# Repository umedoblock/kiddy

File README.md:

# kiddy
some simple device projects designed with KiCad.

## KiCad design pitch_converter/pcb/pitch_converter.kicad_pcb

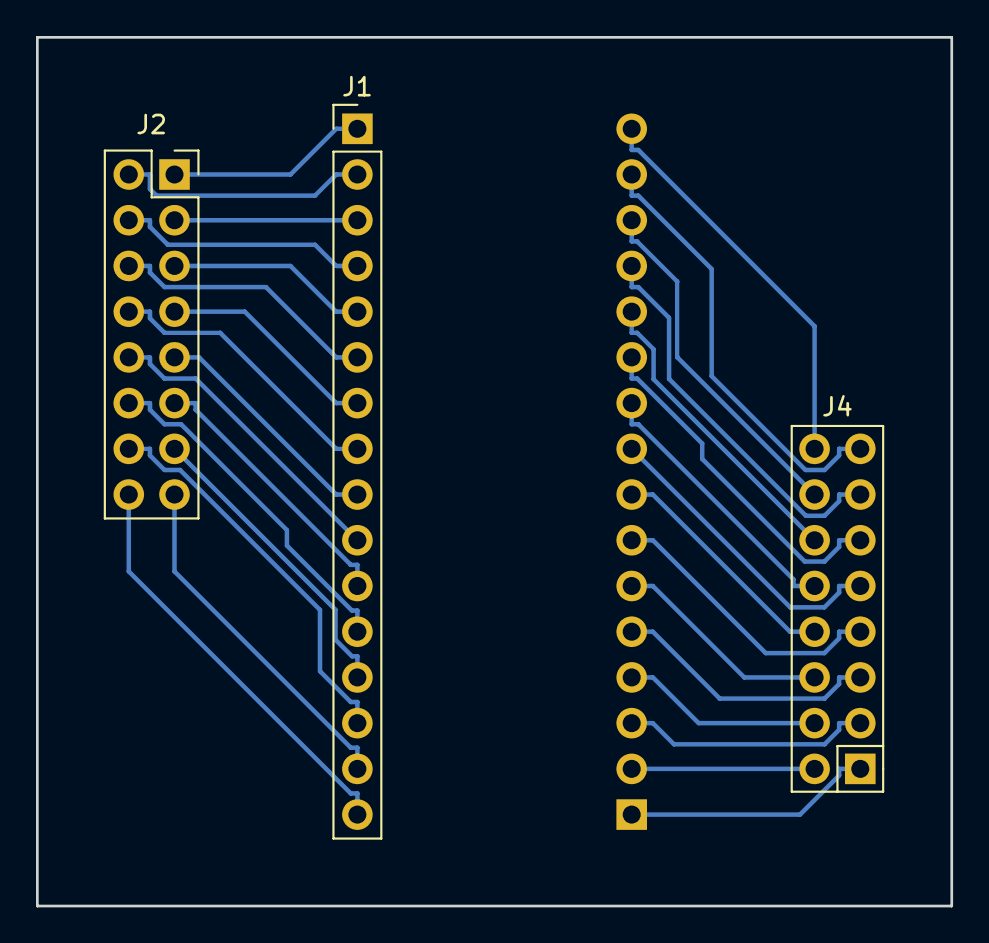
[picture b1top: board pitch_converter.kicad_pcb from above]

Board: 2 copper layers, 50.8 x 48.3 mm, 4 parts (1 on the bottom side), 32 nets.

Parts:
J1, J3: CONN_01X16; PinHeader_1x16_P2.54mm_Vertical
J2: CONN_02X08; PinSocket_2x08_P2.54mm_Vertical
J4: CONN_02X08; PinSocket_2x08_P2.54mm_Vertical_R

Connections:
/C0_1: J1.1, J2.1
/C0_2: J1.2, J2.2
/C0_3: J1.3, J2.3
/C0_4: J1.4, J2.4
/C0_5: J1.5, J2.5
/C0_6: J1.6, J2.6
/C0_7: J1.7, J2.7
/C0_8: J1.8, J2.8
/C0_9: J1.9, J2.9
/C0_10: J1.10, J2.10
/C0_11: J1.11, J2.11
/C0_12: J1.12, J2.12
/C0_13: J1.13, J2.13
/C0_14: J1.14, J2.14
/C0_15: J1.15, J2.15
/C0_16: J1.16, J2.16
/C1_1: J3.1, J4.1
/C1_2: J3.2, J4.2
/C1_3: J3.3, J4.3
/C1_4: J3.4, J4.4
/C1_5: J3.5, J4.5
/C1_6: J3.6, J4.6
/C1_7: J3.7, J4.7
/C1_8: J3.8, J4.8
/C1_9: J3.9, J4.9
/C1_10: J3.10, J4.10
/C1_11: J3.11, J4.11
/C1_12: J3.12, J4.12
/C1_13: J3.13, J4.13
/C1_14: J3.14, J4.14
/C1_15: J3.15, J4.15
/C1_16: J3.16, J4.16

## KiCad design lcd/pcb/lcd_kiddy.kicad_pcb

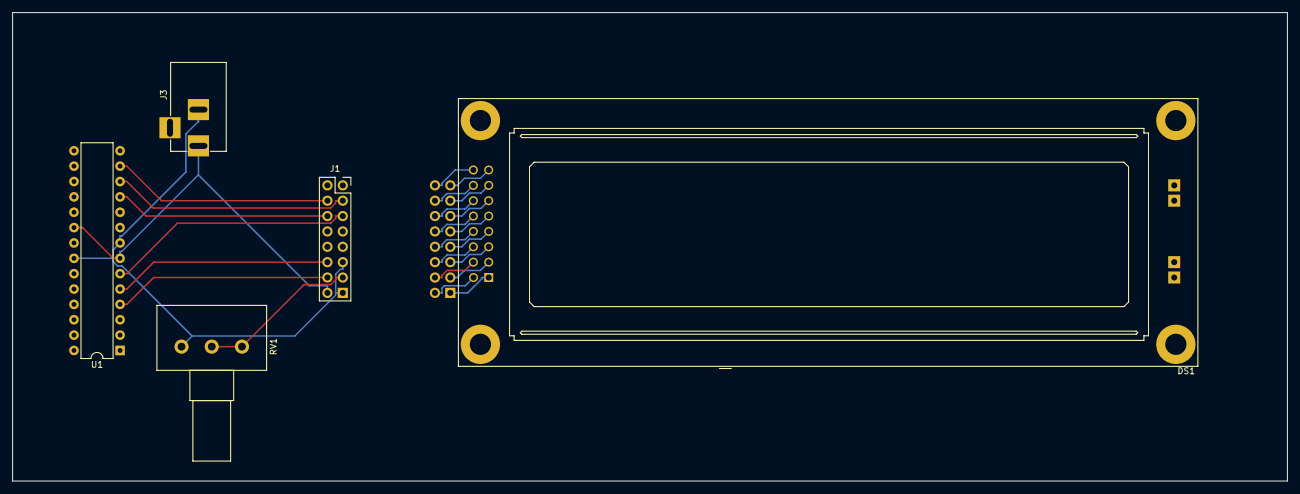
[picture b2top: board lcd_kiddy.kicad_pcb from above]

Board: 2 copper layers, 210.8 x 77.5 mm, 6 parts (1 on the bottom side), 25 nets.

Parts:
DS1: LCD8X2; LCD-2x8-AK
J1: CONN_02X08; PinSocket_2x08_P2.54mm_Vertical_R
J2: CONN_02X08; PinHeader_2x08_P2.54mm_Vertical_R
J3: BARREL_JACK
RV1: 5k; Potentiometer_Alps_RK163_Single_Horizontal
U1: ATMEGA328-PU; DIP-28_W7.62mm

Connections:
+5V: J1.2, J3.1, U1.7, U1.20
/D0: DS1.7, J2.7
/D1: DS1.8, J2.8
/D2: DS1.9, J2.9
/D3: DS1.10, J2.10
/D4: DS1.11, J2.11
/D5: DS1.12, J2.12
/D6: DS1.13, J2.13
/D7: DS1.14, J2.14
/E: DS1.6, J2.6
/LED+: DS1.15, J2.15
/LED-: DS1.16, J2.16
/PD2: J1.4, U1.4
/PD3: J1.6, U1.5
/PD4: J1.11, U1.6
/PD5: J1.12, U1.11
/PD6: J1.13, U1.12
/PD7: J1.14, U1.13
/R/W: DS1.5, J2.5
/RS: DS1.4, J2.4
/VDD: DS1.2, J2.2
/VEE: DS1.3, J2.3
/VSS: DS1.1, J2.1
GND: J1.1, J1.5, J3.2, RV1.1, U1.8, U1.22
unnamed: J1.3, RV1.2, RV1.3

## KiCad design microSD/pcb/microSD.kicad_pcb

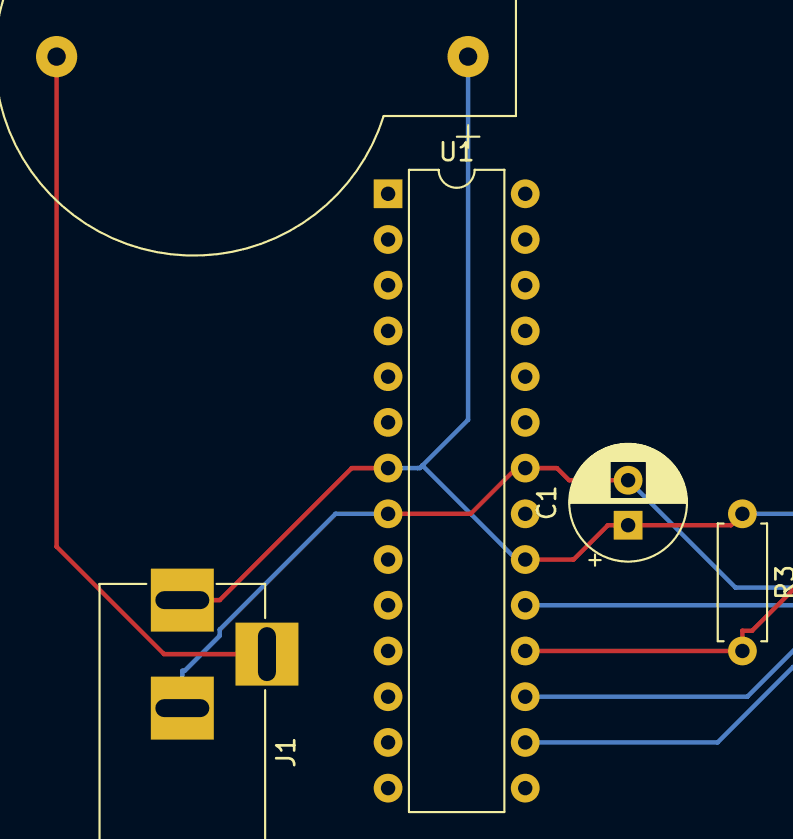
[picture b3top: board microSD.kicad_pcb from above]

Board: 2 copper layers, 6 parts (1 on the bottom side), 7 nets.

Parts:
BT1: Battery_Cell; BatteryHolder_CR2032H
C1: 1u; CP_Radial_D6.3mm_P2.50mm
J1: BARREL_JACK
J4: Micro_SD_Card_Det_SPI; microSD_HC_Hirose_DM3AT-SF-PEJM5
R3: 10k; R_Axial_DIN0207_L6.3mm_D2.5mm_P7.62mm_Horizontal
U1: ATMEGA328P-PU; DIP-28_W7.62mm

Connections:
+3V3: BT1.1, C1.1, J1.1, J4.4, R3.1, U1.7, U1.20
/MISO: J4.7, R3.2, U1.18
/MOSI: J4.3, U1.17
/SCLK: J4.5, U1.19
/_SS: J4.2, U1.16
GND: C1.2, J1.2, J4.6, U1.8, U1.22
unnamed: BT1.2, J1.3

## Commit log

2018-01-03 add tiny comment.
2018-01-03 set ignore files about KiCad.
2018-01-03 pcb files to make a board. eeschema is completed.
2018-01-07 chaN library.
2018-01-18 20x02 のLCDに対応。
2018-01-18 bus 幅を4に設定。
2018-01-18 一旦，LCDの制御boardは完成とする。
2018-01-18 引っ越し。
2018-01-18 basic lcd kiddy files.
2018-01-19 change one tab to four spaces.
2018-01-19 現状，上段の全ての桁に黒四角が表示される。書き込み成功版。
2018-01-19 unsigned char の上位4bitを逆順にする。下位4bitは0で埋める。
    出力は以下の通り。
    d[ 0]=0b00000000, r[ 0]=0b00000000
    d[ 1]=0b00010000, r[ 1]=0b10000000
    d[ 2]=0b00100000, r[ 2]=0b01000000
    d[ 3]=0b00110000, r[ 3]=0b11000000
    d[ 4]=0b01000000, r[ 4]=0b00100000
2018-01-19 4bit mode で lcd に書き込む時，上位4bitの並びを逆順にする。
    下位4bitは0で埋める。
2018-01-19 unsigned char の上位4bitを逆順に並び替える際，下位4bitを変更しない。
2018-01-19 d[], r[] の大きさを16で固定するのではなくて，macro定義にした。
2018-01-19 d[] の値を左に4bitずらしていた箇所を削除。
2018-01-19 d[i]=i; として，d[i] の初期値をiとした。
2018-01-19 出力をざっと見た感じ，8bitsを逆順にしてくれているので，bugはないでしょう。
2018-01-19 PD6-7を LCDの制御PIN(R/W, RS)に割り当てていたため，PINの割当を大幅に変更。
    要するに，大改造。
    bread boardの配線で検証できていなければならない問題であったと反省。
    変更が必要となった理由。
    LCDの制御を4bit modeで行う。この場合，P?7-4のいずれかをLCDの制御PINに
    割り当ててしまうとChaN氏のlibraryを使えない。
    何故ならば，P?7-4はChaN氏のlibraryの4bit modeにおいて，
2018-01-20 PD4-7を4bit busに，PD3->E, PD2->RSの制御に割り当てた。
    ChaN氏の図示する配線と同じにしたつもり。
    http://elm-chan.org/fsw/ezlcd/00index_j.html
2018-01-20 配線をChaN氏の説明と同じにした。
    ただし，使用するPORTをPORTDにしている。ChaN氏の説明ではPORTB。
    http://elm-chan.org/fsw/ezlcd/00index_j.html
2018-01-20 4bit mode で書き込みをする時，下位4bitの内容を変更しないように修正。
    http://elm-chan.org/fsw/ezlcd/00index_j.html
    のマクロ記述をそのまま書いただけなんだけど。。。
2018-01-20 配線作業時に使用する。配線のメモ用紙にする。
2018-01-20 add ignore files for make.
2018-01-20 add ignore file for make.
2018-01-20 rules for Pcbnew
2018-01-20 tags set to ignore file.
2018-01-20 LCDの表示部が基板の上空を通過するよう部品の配置を修正。付随して配線も修正。
2018-01-20 LCDの表示部が基板の上を通過するように修正した時のcommit漏れ。
2018-01-20 部品を上部にまとめた完成版。部品の干渉がないよう配置を工夫した。
2018-01-24 change directory hierarchy.
2018-01-25 "4bit mode" の囲いを削除。
2018-02-08 Thanks ChaN. add ChaN's fatfs library.
2018-02-08 atmega328p に書き込めば，microSDに書き込めるfirmware。
2018-02-08 atmega328p can write simple message to microSD.
2018-02-08 ignore that make command create temporary directory.
2018-02-08 atmega328p の pin assign に関する定義は別のheaderに書くことにした。
2018-02-08 change a tab to some spaces.
2018-02-08 use MACRO to avoid cloned expression.
2018-02-08 change a explain.
2018-02-08 key-value style で，任意の内容をLCDへ出力できる。
2018-02-08 LCDとatmega168aの配線方法を書いた。
2018-02-09 fix typo.
2018-02-10 add atmega88 setting.
2018-02-10 add describe_value() function for convinient to out put log.
2018-02-10 5k ohm potentionmeter connect VEE and GND.
2018-02-10 VEEとGNDを5kの可変抵抗で接続するようにした。
2018-02-11 descrive master and slave relative.
2018-02-14 count=0 -> count=9をmicroSDに書き込む。
2018-02-14 f_open() に成功してから，文字列をmicroSDに書き込むように修正。
    res=f_printf();
    などと書いているから余計なbugを埋め込んでしまっていた。
    反省。
2018-02-24 connect 16x1 with 8x2 Pins.
2018-02-24 for autoroute.
2018-02-24 moved.
2018-02-24 change kiddy.pretty path from abs path to relative path.
2018-02-24 forget a change reason.
    :-)
2018-02-24 check what macro(_USE_XXX_SPI) select.
2018-02-24 make に渡すSPI_LIBの値によって，SPI 通信で使用するlibを切り替えれるようにした。
    default is
    SPI_LIB=_USE_CHAN_SPI
    If you want to use AVR SPI communication, please use below command.
    $ make SPI_LIB=_USE_AVR_SPI
2018-02-24 forget.
2018-02-24 kiddy library and footprints.
2018-02-24 change _USE_AVR_SPI meaning to #error.
